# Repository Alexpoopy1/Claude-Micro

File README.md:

# Claude Micro

A 13-key agent macropad on clear MX switches: six frosted status keys, seven
command keys, a rotary reasoning dial, a planar joystick, a five-pad capacitive touch
strip and a 19-LED RGB chain. Fully printable, fully routed, fully checked.

Design study of the [Work Louder × OpenAI Codex Micro][codex] — same feature
set (13 switches, 1 encoder, 1 planar joystick, 1 touch sensor, 6 agent keys),
rebuilt from scratch as open hardware with the Claude mark on the front.

[codex]: https://openai.com/supply/co-lab/work-louder/

```
make            # build everything, then verify it
open build/claude-micro.html
```

Deploying to Vercel serves the same file: `vercel.json` runs the STL, PCB and
HTML build steps and publishes `build/` as the site, with `/` rewritten to
`claude-micro.html`. No framework, no Node build — just the Python tooling
above, so the deployed page is always generated fresh from
`config/device.json` rather than a stale checked-in copy.

## What you get

| Output | Where | What it is |
| --- | --- | --- |
| **Interactive viewer** | `build/claude-micro.html` | One self-contained file: WebGL model with an exploded-view slider, PCB layer viewer, schematic, BOM, print guide, firmware reference and the full check report. No network, no CDN. |
| **Printable parts** | `build/stl/*.stl` | 9 parts, 22 pieces, ~88 g of filament. Every one proven watertight before it is written. |
| **PCB** | `build/pcb/claude-micro.kicad_pcb` | Open in KiCad 7/8. Placed, routed, poured, zoned. Also `.kicad_sch`, `.kicad_pro`, `.net`. |
| **EasyEDA schematic** | `build/pcb/claude-micro-easyeda.json` | `make easyeda`. Opens in EasyEDA (File → Open → EasyEDA) and imports into EasyEDA Pro via File → Import → EasyEDA Standard — for publishing to OSHWLab or ordering through JLCPCB. |
| **Fabrication** | `build/pcb/gerbers/` | RS-274X gerbers for all nine layers plus separate plated and non-plated Excellon drill files. Upload as-is. |
| **Assembly** | `build/pcb/bom.csv`, `positions.csv` | 18 BOM lines, 89 components, pick-and-place positions. |
| **Firmware** | `firmware/qmk/claude_micro/` | Drop-in QMK keyboard folder. |
| **Reports** | `build/pcb/drc_report.json`, `build/stl_report.json` | Machine-readable results of every check. |

## Hardware

|  |  |
| --- | --- |
| Keys | 13 × clear-housing MX switches, 5-pin PCB mount, on a 19.05 mm grid — 6 agent, 7 command |
| Dial | EC11E rotary encoder with push, on a 26 mm knurled knob |
| Joystick | 20 mm 2-axis analog thumbstick into ADC0/ADC1, click on its own pin |
| Touch | 5-pad strip read by RC charge time — no touch controller |
| RGB | 19 × SK6812 (13 per-key + 6 underglow), 5 V through a 74LVC1G17 buffer |
| MCU | RP2040 module, Raspberry Pi Pico form factor (USB-C variant recommended) |
| Board | 159 × 102 mm, 2 layer, 1.6 mm, 0.2 mm rules |
| Case | 165 × 108 × 19.5 mm printed two-piece, 6° tilt feet |

### Agent keys

The six frosted keys mirror six host threads. The host pushes state over raw
HID and the board renders it:

| State | Colour | |
| --- | --- | --- |
| idle | white | nothing running |
| thinking | blue, breathing | model is reasoning |
| running | light blue, breathing | tools are executing |
| waiting | amber | needs your input |
| done | green | finished cleanly |
| error | red | failed |

If the host goes quiet for 30 s every key falls back to idle, so a crashed
bridge never leaves stale status on the desk.

### The dial

Turning it walks reasoning effort — low → medium → high → max. Pressing it is
an ordinary matrix key (row 3, col 1), so it can be remapped like any other.

## How it is built

Everything derives from **`config/device.json`**. Change the key pitch there
and the STLs, the board, the firmware descriptors and the viewer all move
together; the test suite fails if any of them disagree.

```
config/device.json      one source of truth
        │
tools/  device.py       loader + derived layout (LED chain, matrix nodes, pads)
        mesh.py         watertight mesh kernel (no CSG, no dependencies)
        parts.py        every physical part, printable and purchased
        circuit.py      schematic as data: components, footprints, nets
        router.py       grid maze router + copper pour generator
        build_pcb.py    place → route → pour → check
        outputs.py      KiCad, gerbers, Excellon, BOM, board.json
        checks.py       ERC + DRC + mechanical fit
        schematic.py    SVG schematic
        build_easyeda.py   schematic → EasyEDA Standard source
        build_stl.py    printable parts → binary STL
        build_html.py   the single-file viewer
        build_firmware.py  QMK descriptors
tests/  test_all.py     36 checks across geometry, layout, circuit and board
```

No third-party packages. Python 3.11 standard library only.

### The mesh kernel

There is no CSG. Every solid is built from operations that are watertight by
construction — polygon extrusion, lofting, and lathing — and the awkward case
(capping an outline riddled with holes) is handled by a trapezoidal scanline
decomposition that re-subdivides the side walls so caps and walls share exactly
the same vertices. `Mesh.validate()` then *proves* each part is a closed,
consistently oriented 2-manifold with positive volume, and `build_stl.py`
refuses to write a file that fails.

### The router

The board is rasterised onto a 0.2 mm grid where every piece of copper is
stamped along with its clearance halo, so "may net N occupy this cell?" is one
array lookup. Nets are then routed shortest-first with A* over that grid, with
a cost for changing layer and a separate keepout map that stops a via being
drilled too close to another hole. Leftover free space becomes the ground pour,
emitted as scanline runs. Any GND pad the pour cannot reach gets found by a
flood fill and routed in with a track — the same flood fill the DRC uses, so
the fixer and the checker cannot drift apart.

## Verification

`make test` runs 36 checks:

* **Geometry** — kernel invariants, analytic volume checks, a fuzz pass over
  random hole patterns, and every printable part proven watertight, manifold,
  correctly oriented, printer-sized and thick enough to print.
* **Layout** — key pitch, top-surface collisions, bezel window clearances, a
  monotonic Z stack, and that the encoder shaft does not bottom out in the knob.
* **Circuit** — ERC, one switch and one diode per matrix node, unique matrix
  addresses, an unbroken LED chain, no double-booked GPIO, the LED rail fused
  and level-shifted, the touch strip fully wired.
* **Board** — every connection routed, ≥ 0.2 mm copper clearance verified on a
  fresh raster of the finished geometry, annular rings, hole-to-hole spacing,
  all copper inside the profile, the ground pour reaching every GND pad, no
  courtyard overlaps, and nothing under the MCU module taller than its standoff.
* **Outputs** — balanced s-expressions in the KiCad files, well-formed gerbers
  and Excellon, drill counts matching the board, the BOM covering every
  component, the viewer free of external references, and the firmware agreeing
  with the config on pins, LED count, layers and layout size.
* **EasyEDA** — every shape string matching EasyEDA's documented field order,
  no duplicate ids, and the connectivity rebuilt out of the exported file the
  way EasyEDA reads it — pin dot → wire → net label — coming back identical to
  the source netlist, all 265 pads and 68 nets.

Current status: **0 DRC errors, 0 warnings, 141/141 connections routed, 9/9
meshes watertight.**

## Building one

1. **Print** at 0.2 mm, 3 walls, 25% infill. No supports on any part. Print the
   six agent keycaps in natural or clear filament — the roof is 1.0 mm so the
   status colour reads through. All 13 caps take a standard MX cross stem, so
   bought keycaps drop straight in if you would rather not print them.
2. **Order the PCB** — upload `build/pcb/gerbers/` as a zip. Nothing exotic:
   2 layer, 1.6 mm, 0.2 mm track and clearance.
3. **Populate** — bottom side first (diodes, 0603s, the SOT-23-5, then the
   RP2040 module on a 2.54 mm header), then the top: the 19 SK6812s, then the
   13 MX switches, the EC11 and the thumbstick. Seat every switch fully — the
   two locating posts must bottom out before you solder, or the plate will not
   sit flat.
4. **Flash** — `qmk compile -kb claude_micro -km default`, hold BOOTSEL, copy
   the UF2 across.
5. **Assemble** — six M2 heat-set inserts in the bezel, drop the diffuser into
   the touch window, six M2 × 6 mm screws from underneath.

Full step-by-step with per-part orientation is in the viewer's
**Print & assemble** tab.

## Licence

Hardware and firmware are open. The Claude mark is Anthropic's; it is used here
on a personal build, not a product for sale.

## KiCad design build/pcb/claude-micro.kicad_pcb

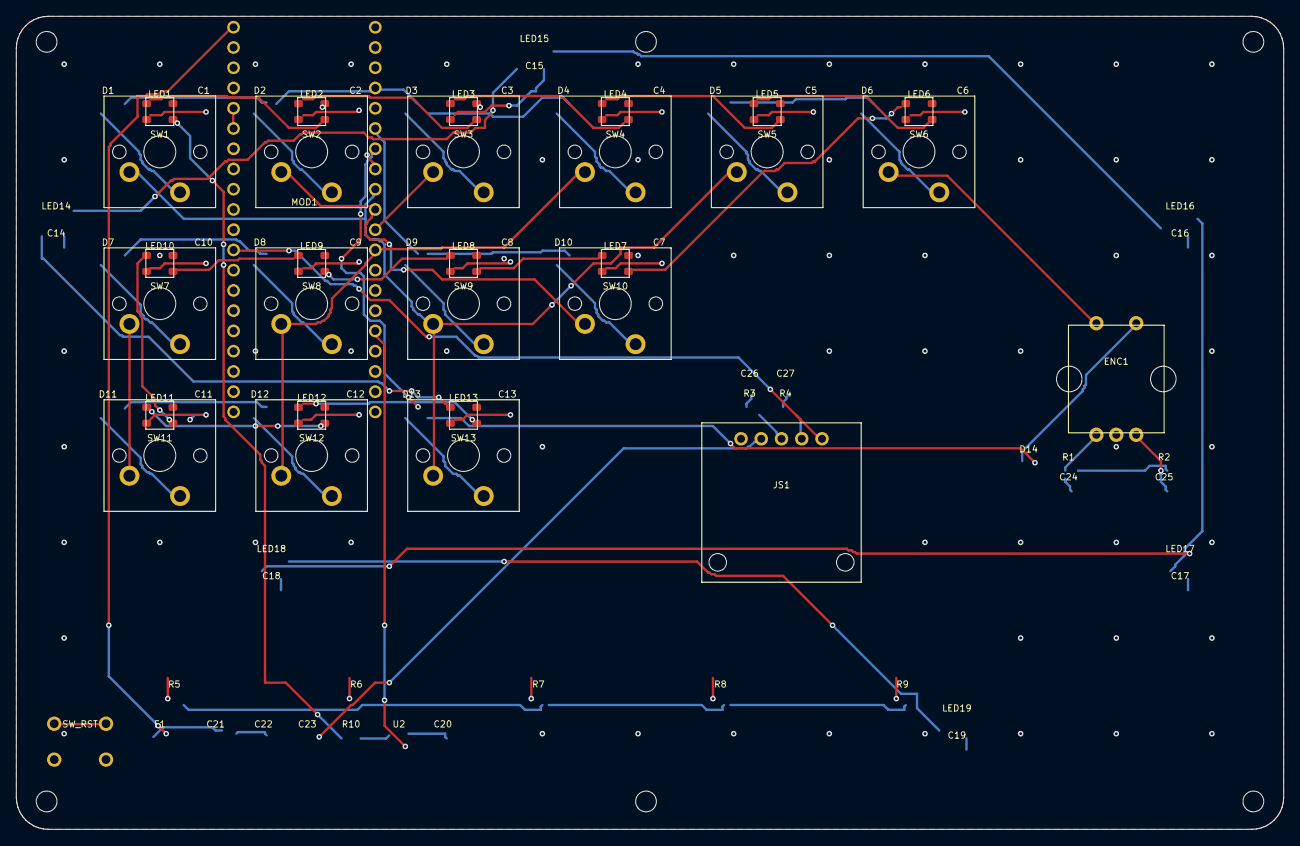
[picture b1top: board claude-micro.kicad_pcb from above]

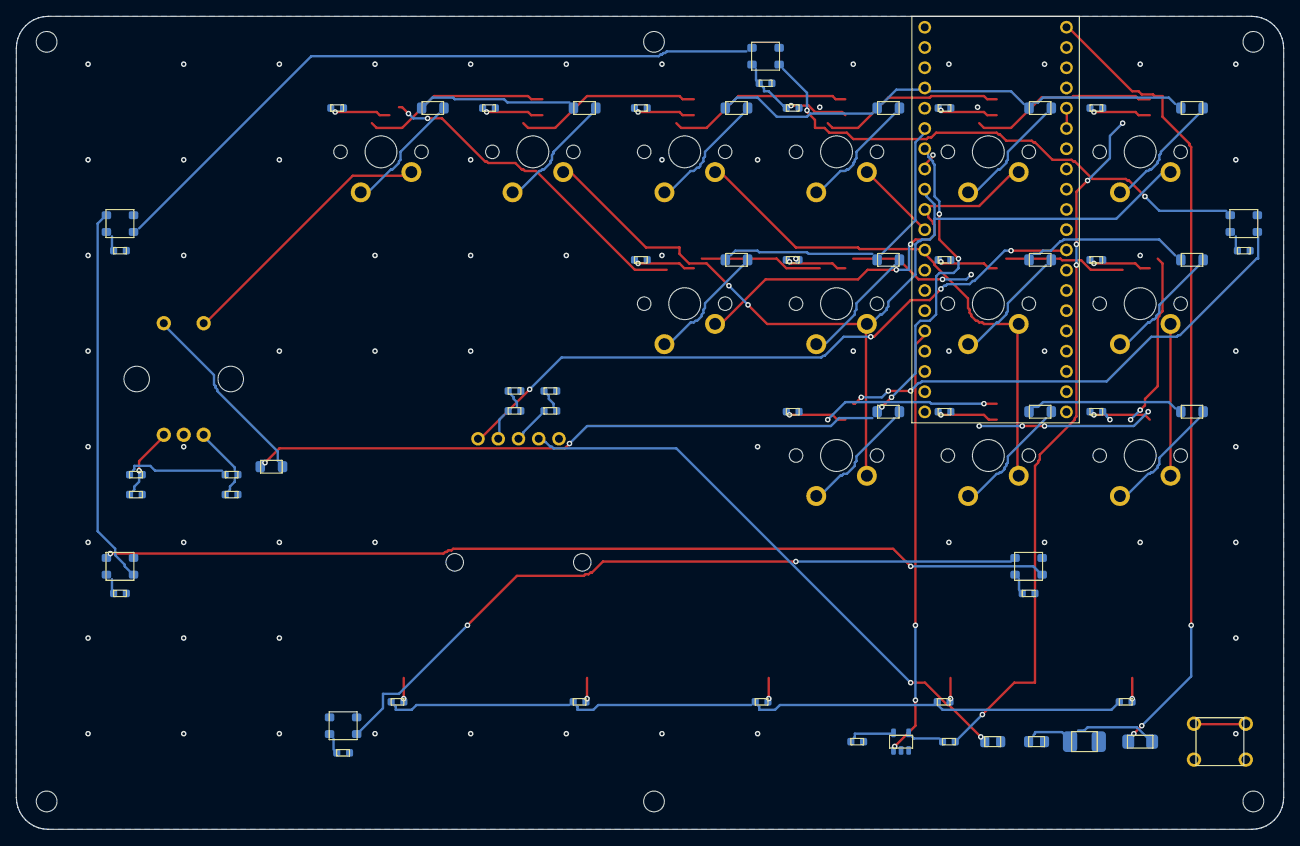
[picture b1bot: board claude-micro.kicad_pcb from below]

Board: 2 copper layers, 159.0 x 102.0 mm, 89 parts (61 on the bottom side), 61 nets.

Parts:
C1, C2, C3, C4, C5, C6, C7, C8, C9, C10, C11, C12, C13, C14, C15, C16, C17, C18, C19, C20, C24, C25: 100nF; C_0603
C21: 470uF 10V; C_1210_BULK
C22, C23: 10uF; C_0805
C26, C27: 10nF; C_0603
D1, D2, D3, D4, D5, D6, D7, D8, D9, D10, D11, D12, D13, D14: 1N4148W; D_SOD123
ENC1: EC11E + switch; EC11E
F1: 1.1A PPTC; F_1206
JS1: 2-axis analog thumbstick; Joystick_20mm
LED1, LED2, LED3, LED4, LED5, LED6, LED7, LED8, LED9, LED10, LED11, LED12, LED13: SK6812MINI-E; SK6812MINI
LED14, LED15, LED16, LED17, LED18, LED19: SK6812-3535; SK6812_3535
MOD1: RP2040 Pico-form-factor module; RP2040_Module_Pico
R1, R2: 10k; R_0603
R3, R4: 1k; R_0603
R5, R6, R7, R8, R9: 1M; R_0603
R10: 470R; R_0603
SW1, SW2, SW3, SW4, SW5, SW6, SW7, SW8, SW9, SW10, SW11, SW12, SW13: MX clear; MX_PCB
SW_RST: Reset; SW_Push_6mm
U2: 74LVC1G17; SOT-23-5

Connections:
+3V3: C23.1, JS1.2, MOD1.35, MOD1.36, R1.1, R2.1
+5V: C1.1, C2.1, C3.1, C4.1, C5.1, C6.1, C7.1, C8.1, C9.1, C10.1, C11.1, C12.1, C13.1, C14.1, C15.1, C16.1, C17.1, C18.1, C19.1, C20.1, C21.1, C22.1, F1.2, LED1.1, LED2.1, LED3.1, LED4.1, LED5.1, LED6.1, LED7.1, LED8.1, LED9.1, LED10.1, LED11.1, LED12.1, LED13.1, LED14.1, LED15.1, LED16.1, LED17.1, LED18.1, LED19.1, U2.5
COL0: MOD1.9, SW1.1, SW5.1, SW9.1, SW13.1
COL1: ENC1.S1, MOD1.10, SW2.1, SW6.1, SW10.1
COL2: MOD1.11, SW3.1, SW7.1, SW11.1
COL3: MOD1.12, SW4.1, SW8.1, SW12.1
ENC_A: C24.1, ENC1.A, MOD1.14, R1.2
ENC_B: C25.1, ENC1.B, MOD1.15, R2.2
GND: C1.2, C2.2, C3.2, C4.2, C5.2, C6.2, C7.2, C8.2, C9.2, C10.2, C11.2, C12.2, C13.2, C14.2, C15.2, C16.2, C17.2, C18.2, C19.2, C20.2, C21.2, C22.2, C23.2, C24.2, C25.2, C26.2, C27.2, ENC1.C, JS1.1, LED1.3, LED2.3, LED3.3, LED4.3, LED5.3, LED6.3, LED7.3, LED8.3, LED9.3, LED10.3, LED11.3, LED12.3, LED13.3, LED14.3, LED15.3, LED16.3, LED17.3, LED18.3, LED19.3, MOD1.3, MOD1.8, MOD1.13, MOD1.18, MOD1.23, MOD1.28, MOD1.33, MOD1.38, SW_RST.3, SW_RST.4, U2.2
JOY_SW: JS1.5, MOD1.29
JOY_X: C26.1, MOD1.31, R3.2
JOY_XR: JS1.3, R3.1
JOY_Y: C27.1, MOD1.32, R4.2
JOY_YR: JS1.4, R4.1
K_A1: D1.2, SW1.2
K_A2: D2.2, SW2.2
K_A3: D3.2, SW3.2
K_A4: D4.2, SW4.2
K_A5: D5.2, SW5.2
K_A6: D6.2, SW6.2
K_ENC_SW: D14.2, ENC1.S2
K_K1: D7.2, SW7.2
K_K2: D8.2, SW8.2
K_K3: D9.2, SW9.2
K_K4: D10.2, SW10.2
K_K5: D11.2, SW11.2
K_K6: D12.2, SW12.2
K_K7: D13.2, SW13.2
LED_D1: LED1.2, LED2.4
LED_D2: LED2.2, LED3.4
LED_D3: LED3.2, LED4.4
LED_D4: LED4.2, LED5.4
LED_D5: LED5.2, LED6.4
LED_D6: LED6.2, LED7.4
LED_D7: LED7.2, LED8.4
LED_D8: LED8.2, LED9.4
LED_D9: LED9.2, LED10.4
LED_D10: LED10.2, LED11.4
LED_D11: LED11.2, LED12.4
LED_D12: LED12.2, LED13.4
LED_D13: LED13.2, LED14.4
LED_D14: LED14.2, LED15.4
LED_D15: LED15.2, LED16.4
LED_D16: LED16.2, LED17.4
LED_D17: LED17.2, LED18.4
LED_D18: LED18.2, LED19.4
LED_DIN: LED1.4, R10.2
LED_DIN_3V3: MOD1.16, U2.1
LED_DIN_5V: R10.1, U2.4
RESET: MOD1.30, SW_RST.1, SW_RST.2
ROW0: D1.1, D2.1, D3.1, D4.1, MOD1.4
ROW1: D5.1, D6.1, D7.1, D8.1, MOD1.5
ROW2: D9.1, D10.1, D11.1, D12.1, MOD1.6
ROW3: D13.1, D14.1, MOD1.7
TOUCH0: MOD1.21, R5.2
TOUCH1: MOD1.22, R6.2
TOUCH2: MOD1.24, R7.2
TOUCH3: MOD1.25, R8.2
TOUCH4: MOD1.26, R9.2
TOUCH_DRV: MOD1.27, R5.1, R6.1, R7.1, R8.1, R9.1
VBUS: F1.1, MOD1.40

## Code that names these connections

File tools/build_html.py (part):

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  <h2>Layers</h2>
  <table><thead><tr><th>#</th><th>Name</th><th>Purpose</th></tr></thead><tbody>${rows}</tbody></table>
  <h2>Pin map</h2>
  <pre>ROW0..3        ${c.matrix.row_pins.join(', ')}
COL0..3        ${c.matrix.col_pins.join(', ')}
Encoder A/B    ${c.pins.encoder_a}, ${c.pins.encoder_b}
LED data       ${c.pins.led_data}  (through a 74LVC1G17 to 5 V)
Touch drive    ${c.pins.touch_drive}
Touch sense    ${c.pins.touch_sense.join(', ')}
Joystick X/Y   ${c.pins.joy_x}, ${c.pins.joy_y}  (ADC0, ADC1)
Joystick click GP22
Reset          ${c.pins.reset}</pre>
  <p>Build with <span class="mono">qmk compile -kb claude_micro -km default</span>. The
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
